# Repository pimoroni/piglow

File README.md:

The PiGlow is a small add on board for the Raspberry Pi that provides 18 individually controllable LEDs.

Learn more: https://shop.pimoroni.com/products/piglow

This repository contains the library and examples for the PiGlow board.

## Installation

**Full install ( recommended ):**

We've created a super-easy installation script that will install all pre-requisites and get your Piglow up and running in a jiffy. To run it fire up Terminal which you'll find in Menu -> Accessories -> Terminal on your Raspberry Pi desktop like so:

In the new terminal window, run our easy installer by typing:

```bash
curl -sS https://get.pimoroni.com/piglow | bash
```

If you choose to download examples you'll find them in `/home/pi/Pimoroni/piglow/`.

**Library install for Python 3:**

on Raspbian:

```bash
sudo apt-get install python3-piglow
```
other environments: 

```bash
sudo pip3 install piglow
```

**Library install for Python 2:**

on Raspbian:

```bash
sudo apt-get install python-piglow
```
other environments: 

```bash
sudo pip2 install piglow
```

In all cases you will have to enable the i2c bus.

## Documentation & Support

* PiGlow GPIO Pinout - https://pinout.xyz/pinout/piglow
* Function reference - http://docs.pimoroni.com/piglow/
* Get help - http://forums.pimoroni.com/c/support

## Backwards Compatibility

The PiGlow Python library is designed to support examples written for Jason's PiGlow library found here: https://github.com/Boeeerb/PiGlow

It's compatible with the examples, and we've ported some over to show you how it's done.

## Using PiGlow

To use the piglow library, you'll probably want to start by importing it:

```python
import piglow
```

Now, you can turn some LEDs on:

```python
piglow.red(64)
```

Nothing will happen yet, you've got to update PiGlow with your changes. Why? Because it's quicker! If you're setting up a pattern it costs time and resources to redraw every step of that setup to the PiGlow, so we don't do that. Instead you need to call `show` like so:

```python
piglow.show()
```

A bug is a feature you can't turn off, however, so if you want to change that behaviour you can set it after importing piglow:

```python
piglow.auto_update = True
```

This will turn on auto update, refreshing the PiGlow after each change so you don't have to.

## Function Reference

### Settings
* `piglow.auto_update` - Set to True or False, determines if the PiGlow should automatically update after each LED change
* `piglow.clear_on_exit` - Set to True or False, determines if the PiGlow should be cleared on exit

### Colours
* `piglow.white( value from 0 to 255 )`
* `piglow.blue( value from 0 to 255 )`
* `piglow.green( value from 0 to 255 )`
* `piglow.yellow( value from 0 to 255 )`
* `piglow.orange( value from 0 to 255 )`
* `piglow.red( value from 0 to 255 )`

### Arm, Spoke, Leg, they're all the same thing!

`piglow.arm( index from 0 to 2, value from 0 to 255 )`

### Multiple LEDs in various different ways

The `set` method accepts a list of LEDs, a list of values, or a single LED or value, or any permutation therein:

`piglow.set(0, 255)` - sets LED 0 to full brightness

`piglow.set([1,3,5,7,9,11,13,15,17],255)` - sets all odd LEDs to full brightness

`piglow.set(0,[50,50,50])` - let the 3 LEDs starting at index 0 to 50 brightness

## Other support for PiGlow

**Gordon Henderson** (@drogon on Twitter) has very kindly added support for PiGlow into his very popular wiringPi library and even includes a basic command line tool that you can use to control your PiGlow! http://wiringpi.com/dev-lib/piglow/

**Simon Walters** (@cymplecy) has added awesome PiGlow support to his Raspberry Pi GPIO Scratch library: http://cymplecy.wordpress.com/2013/08/12/scratch-gpio-piglow-support/

**Jason Barnett** has put together a great Python class and a load of samples: https://github.com/Boeeerb/PiGlow

**Ben Lebherz** has forked Jasons project and tidied up the code a bit while adding gamma correction: https://github.com/benleb/PyGlow

**Manuel Ernst** has created a Node.js library: https://github.com/zaphod1984/node-piglow

## More information

For more information the datasheet for the SN3218 IC is included in this repository which outlines the complete communication protocol for the chip.

For those wanting to wire up their PiGlow in other ways these are the GPIO pins used by the module:

- P1 & P17 (3V3)
- P2 (5V)
- P14 (GND)
- P3 (SDA)
- P5 (SCL)

## Special Thanks

A special thanks for Jason Barnett for carrying the PiGlow torch with his original library.

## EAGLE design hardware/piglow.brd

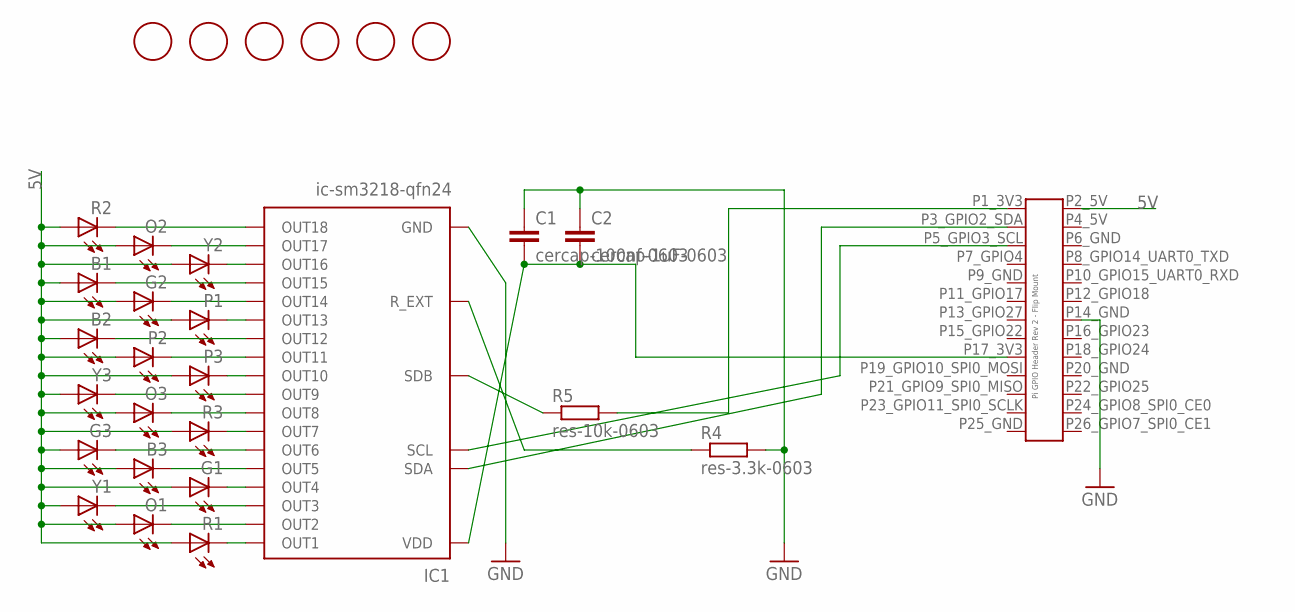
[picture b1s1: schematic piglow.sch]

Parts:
B1, B2, B3: led-blue-0805; CHIPLED_0805
C1: cercap-100nf-0603; C0603K
C2: cercap-1uF-0603; C0603K
G1, G2, G3: led-green-0805; CHIPLED_0805
IC1: ic-sm3218-qfn24; QFN24
O1, O2, O3: led-orange-0805; CHIPLED_0805
P1, P2, P3: led-pink-0805; CHIPLED_0805
R1, R2, R3: led-red-0805; CHIPLED_0805
R4: res-3.3k-0603; R0603
R5: res-10k-0603; R0603@1
U$1, U$2, U$3, U$5, U$6, U$7: FIDUCIAL; FIDUCIAL_1MM
U$4: FCI_89898_313LF_26P_CONNECTOR_SMT_FLIPPED
Y1, Y2, Y3: led-yellow-0805; CHIPLED_0805

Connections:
5V: B1.A, B2.A, B3.A, G1.A, G2.A, G3.A, O1.A, O2.A, O3.A, P1.A, P2.A, P3.A, R1.A, R2.A, R3.A, U$4.P2_5V, Y1.A, Y2.A, Y3.A
GND: C1.1, C2.1, IC1.4 (GND), IC1.GND, R4.2, U$4.P14_GND
unnamed: IC1.6 (SCL), U$4.P5_GPIO3_SCL
unnamed: IC1.5 (SDA), U$4.P3_GPIO2_SDA
unnamed: IC1.24 (SDB), R5.1
unnamed: IC1.1 (OUT18), R2.C
unnamed: IC1.23 (OUT17), O2.C
unnamed: IC1.22 (OUT16), Y2.C
unnamed: B1.C, IC1.21 (OUT15)
unnamed: IC1.7 (OUT1), R1.C
unnamed: IC1.8 (OUT2), O1.C
unnamed: IC1.9 (OUT3), Y1.C
unnamed: G1.C, IC1.10 (OUT4)
unnamed: B3.C, IC1.11 (OUT5)
unnamed: G3.C, IC1.12 (OUT6)
unnamed: IC1.13 (OUT7), R3.C
unnamed: IC1.14 (OUT8), O3.C
unnamed: IC1.15 (OUT9), Y3.C
unnamed: IC1.16 (OUT10), P3.C
unnamed: IC1.17 (OUT11), P2.C
unnamed: IC1.2 (R_EXT), R4.1
unnamed: IC1.19 (OUT13), P1.C
unnamed: B2.C, IC1.18 (OUT12)
unnamed: G2.C, IC1.20 (OUT14)
unnamed: C1.2, C2.2, IC1.3 (VDD), U$4.P17_3V3
P4_5V: U$4.P4_5V
VCC: R5.2, U$4.P1_3V3

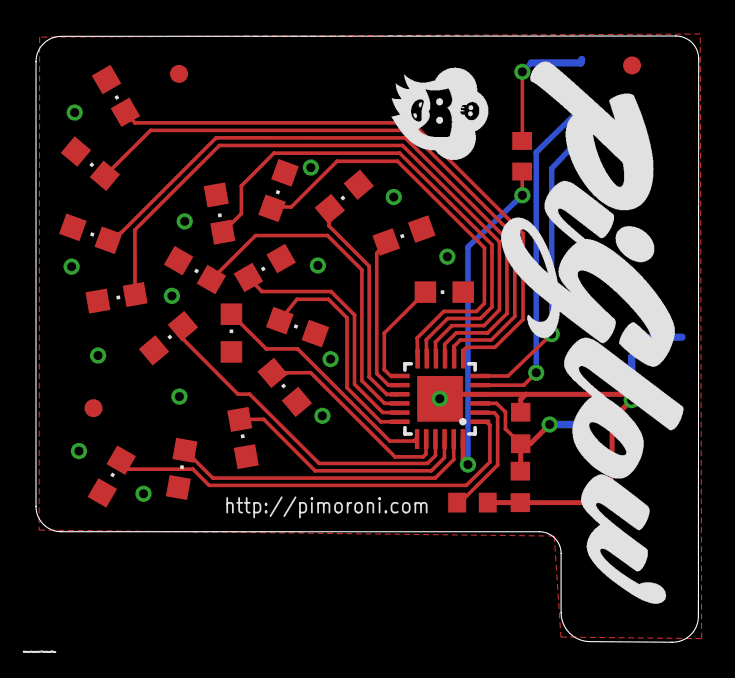
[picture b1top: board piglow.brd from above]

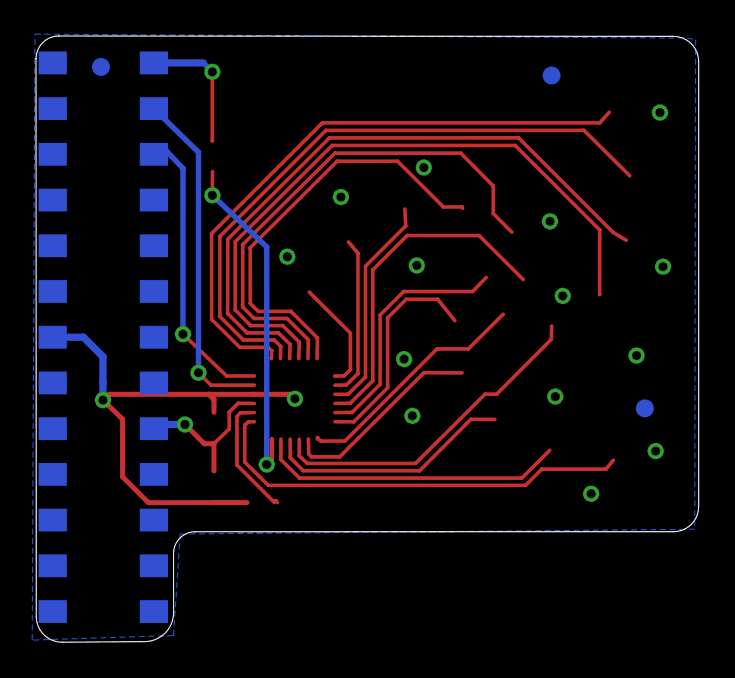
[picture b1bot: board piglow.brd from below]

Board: 2 copper layers, 36.8 x 33.7 mm, 30 parts (4 on the bottom side), 26 nets.

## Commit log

2013-08-12 Setting up i2c instructions
2013-08-12 Added SN3218 datasheet
2013-08-12 Updated instructions and samples
2013-08-12 Minor styling changes
2013-08-12 Added first example code
2013-08-12 Added more information section
2013-08-13 Update to pitglow.py - Turning off the LEDs when exiting
    Small update to clear down all the LEDs upon exiting the script.
2013-08-14 Updated README.md to include GPIO pins used by the PiGlow
2013-08-14 Minor changes to comments
2013-08-14 Auto-detect what I2C bus to use based on the Revision (old Pis need bus 0 not 1)
2013-08-14 Add missing shebang line
2013-08-15 Changed link to the Scratch example code
2013-08-21 Added links to Jason and Bens python libraries
2013-08-23 Corrected Bens' surname
2013-09-18 Added Manuel Ernsts' Node.js library
2013-09-28 Added PCB layout
2013-09-28 Added examples folder
2013-09-28 Added license
2015-02-03 Updated SN3218 to new landings
    Also Tidied up Schematic and rerouted board with 10mil traces and 8mil
    clearance
2015-02-04 Revert "Added license"
    This reverts commit 9893b45acbb942a63296f0416d063dc0881d831a.
2015-02-04 Revert "Updated SN3218 to new landings"
    This reverts commit 9275a731dc1cb28da2cd379615e04127a905d690.
2015-02-04 New SN3218 landing
2015-05-08 Update to new PiGlow library
2015-05-08 Corrected import
2015-05-08 Added logo
2015-05-12 Cleaning up, insanity fixes, tween feature
2015-08-15 Tweaks n fixes
2015-09-28 Tweaks and tidying
2015-10-16 Code tidied
2016-03-11 curl standardisation
2016-05-18 Add `_rings` LED list to PiGlow library
2016-05-18 Autoupdate LEDs within `all` function if `auto_update` is True
2016-05-18 Add `wave driver` example, for creating sine wave effects
2016-07-03 Function Reference
2016-07-03 data sheet moved to data sheet folder
2016-07-03 datasheet to separate folder
2016-07-05 PCB files into hardware dir
2016-07-06 Fixed legs.py for Python3 compatibility
2016-07-12 Added license, bumped version
2016-07-12 Removed ref to pimglow.py in MANIFEST, bumped version
2016-07-18 debian packaging
2016-07-18 extended description reformatted
2016-07-19 PyPi resources straightened
2016-07-19 using master CHANGELOG
2016-07-19 copyright date corrected
2016-07-19 simple README
2016-07-19 formatting tweak
2016-07-19 README with Unix LF
2016-07-24 PEP8 compliant import + try clauses
2016-09-08 Priority changed to extra
2016-11-07 using sys.exit + __version__ in lib
2016-11-08 fix for reponame tracking and package siblings
2016-11-09 fix for setup.py version touch up
2016-11-10 Prep for 1.2.4
2016-11-15 updated install instructions
2016-11-18 Updated docstrings
2016-11-18 Added Sphinx docs
2017-02-08 Prefixed methods with piglow. for #13
2017-04-28 Added MIT license file to root
2017-04-28 Updated MIT license file to Pimoroni Ltd.
2017-05-03 Updated debian package with better descriptions.
2017-05-03 Removed cruft common to Sphinx build tools.
2017-05-03 Fixed headers
2017-09-21 Defer setup
2019-10-27 Fix off-by-one modulo bug in ring() and single()
2019-10-31 Fix tween() default start
    Take a copy instead of a reference to _values, so that start isn't changing
    through the loop.
2019-11-03 Optimize tween
    * Move the floating point division out of the inner loop
    * Use map() / list comprehensions where possible, in preference to nested loop
    * Don't call show() explicitly if _set() already did it
    * Regression test (not committed) shows identical _values being written at each step
2019-11-04 Fix for Python 2.7
2019-11-04 Example to demo tweening
2019-11-04 Prep for v1.2.5

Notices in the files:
parts and their libraries:
pimoroni: Licensing: CC v3.0 Share-Alike You are welcome to use this library for commercial purposes.
